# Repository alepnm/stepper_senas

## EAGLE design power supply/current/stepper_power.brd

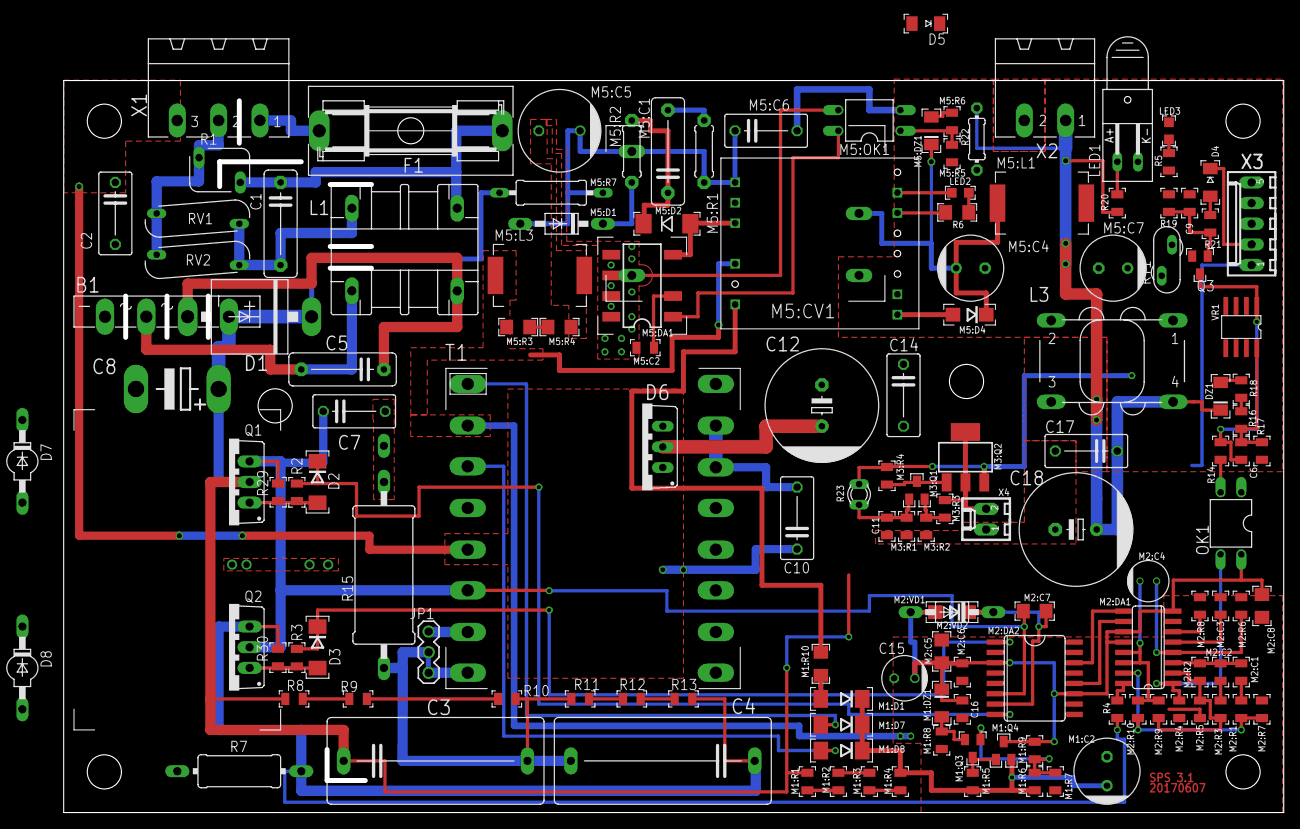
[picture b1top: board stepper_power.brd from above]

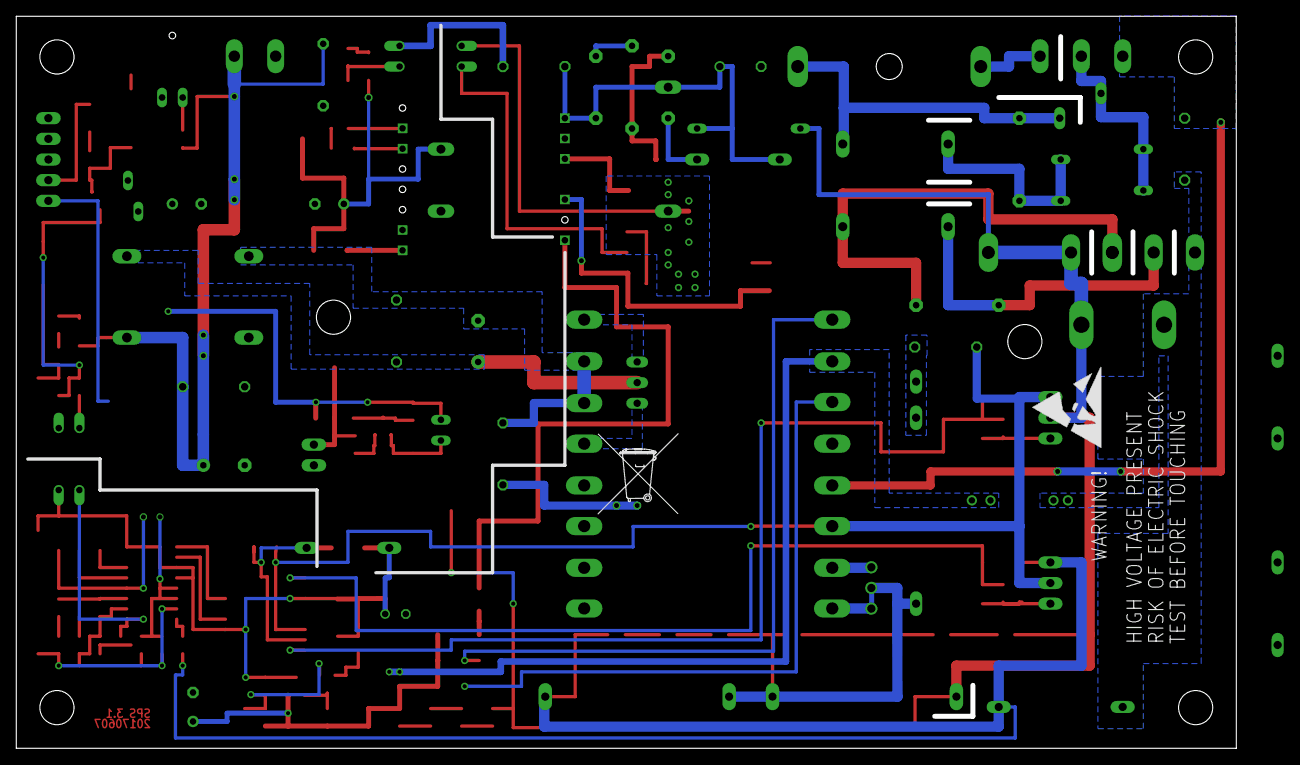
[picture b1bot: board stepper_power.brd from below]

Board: 2 copper layers, 150.0 x 90.0 mm, 143 parts (2 on the bottom side), 88 nets.

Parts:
B1: GBU8K; GBU4S
C1, C5: 0.1/400V; C102-043X133
C2, C10: 2200/3kV; C075-042X103
C3, C4: 1,0uFx275V; C225-108X268
C6, C16: 0.1; C0805
C7: 1n; C075-042X103
C8: 330,0x450V; EB25H
C9, C11: 10n; C0805
C12, C18: 1000x50V; E5-13
C14, C17: 0.1; C075-042X103
C15: 47x16V; E2,5-6E
D1: P600K; P6-15-1
D2, D3: 10MQ100; DO214AA
D4, D5: BAS32; MINIMELF
D6: MUR1620CTG; TO220ABS
D7, D8: BYV27; SOD57-10
DZ1: 12V; SOD80C
F1: 5A; SH22,5A
JP1: 1X03
L1: MFE
L3: 82721K
LED1: VOUT; Q62902-B155
LED2, LED3: 12V; CHIPLED_0805
M1:C2, M5:C4, M5:C7: 100x35V; E3,5-8
M1:D1, M1:D7, M1:D8: 10MQ100; DO214AA
M1:DZ1, M5:DZ1: 12V; SOD80C
M1:Q3: BC817; SOT23-BEC
M1:Q4: BC807; SOT23-BEC
M1:R1, M1:R2, M1:R3, M1:R4, M1:R5, M1:R6, M1:R7, M1:R8, M1:R9, M3:R1, M3:R2, M3:R3, M3:R4, M5:R5, M5:R6: R0805
M1:R10: 120; R1206
M2:C1, M2:C2: 10n; C0805
M2:C3: 4700; C0805
M2:C4: 10x63V; E2-5
M2:C5, M2:C7, M2:C8: 1uF; C1206
M2:C6, M5:C2: 0.1; C0805
M2:DA1: TL494CD; SO16
M2:DA2: IR2113S; SO16L
M2:R1, M2:R3: 33k; R0805
M2:R2: 1M; R0805
M2:R4, M2:R5, M2:R9, M2:R10: 20k; R0805
M2:R6: 10k; R0805
M2:R7: 1k; R0805
M2:R8: 2k; R0805
M2:VD1: UF4007; DO41-10
M2:VD2, M5:D4: 10MQ100; DO214AC
M3:Q1: BC817; SOT23
M3:Q2: BCP52; SOT223
M5:C1: 0.01x630V; C102-043X133
M5:C5: 10.0x400V; E5-10,5
M5:C6: 2200x3kV; C075-042X103
M5:CV1: VSK-S1-5V; VSK-S1
M5:D1: P6KE150; DO41-10
M5:D2: LL4007; MELF-MLL41
M5:DA1: TNY278G; DIP8_1
M5:L1, M5:L3: 1000uH; PLOKSCIAS
M5:OK1: PC817; DIL04
M5:R1: 100; 0207/7
M5:R2: 1k; 0207/7
M5:R3, M5:R4: 1k; R1206
M5:R7: 47; 0309/12
M5:T2: 750841630
OK1: PC817; DIL04
P1: LP_D1.0
Q1, Q2: IRF740; TO220BV
Q3: BC817; SOT23-BEC
R1: S05K275
R2, R3: 30R; R0805
R4, R29, R30: 1k; R0805
R5, R8, R9, R10, R11, R12, R13, R14, R16, R17, R18, R19, R20, R21: R0805
R6: 2k; R1206
R7: 0.1; 0411/15
R15: 100; P0817/22
R22: 10k; 0204/7
R23: P640
RT1: X40
RV1, RV2: 33; TABLETE_10
T1: ETD-39-K-H-16P
U$2: TONNE_10.00
U$3: ESD_10.00
VR1: TL431; SO-08
X1: MAIN; MSTBA3
X2: MSTBA2
X3: Stepper Control; 6410-05
X4: COOLER; 6410-02

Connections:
12VDC: M3:Q2.3, M3:R4.2, M5:C7.+, M5:L1.2, R23.1, RT1.1
12VOUT: R5.1, RT1.2, X3.3
!PS_START: D4.C, X3.2
+V: B1.+, C3.1, C8.+, D1.C, D7.C, M1:R1.2, M5:R7.1, Q1.D, R8.1
AGND: B1.-, C2.2, C8.-, C15.-, C16.2, M1:C2.-, M1:R7.2, M1:R8.2, M2:C3.2, M2:C5.2, M2:C6.1, M2:C8.2, M2:DA1.7, M2:DA2.2, M2:DA2.13, M2:DA2.15, M2:R4.1, M2:R5.1, M2:R6.1, M2:R7.1, M2:R8.1, M5:L3.1, M5:R3.1, M5:T2.4, R7.1, T1.2
COM: C11.2, LED1.K, LED3.C, M3:R1.1, M3:R2.1, M5:C4.-, M5:C6.2, M5:C7.-, M5:CV1.COM, M5:OK1.2, M5:R5.1, M5:T2.8, X2.2, X3.4, X3.5, X4.1
FB: M2:DA1.16, R4.1
GNDP: C9.1, C17.2, C18.-, L3.3, Q3.E, R17.1, R22.2, VR1.2, VR1.3, VR1.6, VR1.7
HO: D2.C, M2:DA2.8, R2.1
LO: D3.C, M2:DA2.1, R3.1
M1:N$1: M1:D1.A, M1:R10.1
M1:N$2: M1:Q3.B, M1:R6.2, M1:R7.1, M1:R9.1
M1:N$3: M1:DZ1.A, M1:Q3.E, M1:R8.1
M1:N$4: M1:Q3.C, M1:Q4.B, M1:R5.2
M1:N$5: M1:R3.1, M1:R4.2
M1:N$6: M1:C2.+, M1:D1.C, M1:D7.C, M1:D8.C, M1:Q4.E, M1:R4.1, M1:R5.1, M1:R6.1
M1:N$8: M1:R1.1, M1:R2.2
M1:N$9: M1:R2.1, M1:R3.2
M2:N$1: M2:DA1.9, M2:DA2.14
M2:N$2: M2:DA1.10, M2:DA2.12
M2:N$3: M2:C7.1, M2:DA2.7, M2:VD1.C, M2:VD2.C
M2:N$4: M2:DA1.6, M2:R8.2
M2:N$5: M2:C3.1, M2:DA1.5
M2:N$6: M2:C1.1, M2:R1.2
M2:N$7: M2:C1.2, M2:C2.1, M2:DA1.3, M2:R2.1
M2:N$8: M2:DA1.2, M2:R2.2, M2:R3.2, M2:R5.2, M2:R9.1
M2:N$9: M2:C4.+, M2:DA1.13, M2:DA1.14, M2:R9.2, M2:R10.2
M2:N$10: M2:C2.2, M2:R3.1
M2:N$11: M2:DA1.15, M2:R1.1, M2:R7.2, M2:R10.1
M2:N$12: M2:C4.-, M2:DA1.4, M2:R6.2
M3:N$1: M3:Q1.2, M3:R2.2, M3:R3.1
M3:N$2: M3:Q1.3, M3:Q2.1, M3:R4.1
M5:AGND: M5:C2.2, M5:C5.-, M5:CV1.AC2, M5:DA1.5, M5:DA1.6, M5:DA1.7, M5:DA1.8, M5:L3.2, M5:OK1.3, M5:R4.2
M5:N$1: M5:C1.2, M5:R1.1
M5:N$2: M5:D1.C, M5:R2.2
M5:N$3: M5:C5.+, M5:C6.1, M5:CV1.AC1, M5:D1.A, M5:R1.2, M5:R7.2, M5:T2.1
M5:N$4: M5:C1.1, M5:D2.C, M5:R2.1
M5:N$5: M5:C2.1, M5:DA1.2
M5:N$6: M5:D2.A, M5:DA1.4, M5:T2.3
M5:N$7: M5:C4.+, M5:CV1.VDC, M5:D4.C, M5:DZ1.C, M5:L1.1
M5:N$8: M5:DA1.1, M5:OK1.4
M5:N$10: M5:D4.A, M5:T2.7
M5:N$13: M5:OK1.1, M5:R5.2, M5:R6.1
M5:N$15: M5:R3.2, M5:R4.1
M5:N$16: M5:DZ1.A, M5:R6.2
unnamed: OK1.2, R14.2
unnamed: R11.1, R12.1
unnamed: M5:T2.12, R6.2
unnamed: C3.2, C4.2, JP1.2, R10.2, R11.2, R15.1
unnamed: C7.2, P1.P$1, R15.2
unnamed: D3.A, Q2.G, R3.2, R30.1
unnamed: D6.3, T1.16
unnamed: D6.1, T1.13
unnamed: C6.2, R16.2, R17.2, VR1.8
unnamed: DZ1.A, R18.1
unnamed: C10.2, C12.-, C14.1, L3.2, T1.14, T1.15
unnamed: C9.2, Q3.B, R19.2, R21.2
unnamed: C12.+, C14.2, D6.2, L3.1
unnamed: LED3.A, R5.2
unnamed: D2.A, Q1.G, R2.2, R29.1
unnamed: D4.A, R21.1
unnamed: C11.1, M3:Q1.1, M3:R1.2, R23.2
unnamed: R12.2, R13.2
unnamed: JP1.1, T1.7
unnamed: M3:Q2.2, M3:Q2.4, M3:R3.2, X4.2
unnamed: JP1.3, T1.8
unnamed: D5.C, LED2.A, R6.1
unnamed: D5.A, LED2.C, M5:T2.13
unnamed: R9.1, R10.1
unnamed: R8.2, R9.2
unnamed: LED1.A, R20.1
unnamed: C1.2, L1.3, RV1.1, RV2.1
unnamed: C1.1, F1.2, L1.2, R1.2
unnamed: R1.1, RV1.2, RV2.2, X1.2
unnamed: F1.1, X1.1
unnamed: C6.1, Q3.C, R14.1, VR1.1
unnamed: B1.AC2, C5.2, L1.4
unnamed: R16.1, R18.2
unnamed: C4.1, D8.A, Q2.S, R4.2, R7.2, R13.1, R30.2
unnamed: B1.AC1, C5.1, D1.A, L1.1
OKE: M2:DA1.1, M2:R4.2, OK1.3
PE: C2.1, C10.1, T1.5, X1.3
TRA: M1:D8.A, T1.3
TRB: M1:D7.A, T1.1
VB: C7.1, D7.A, D8.C, M2:C7.2, M2:DA2.6, Q1.S, Q2.D, R29.2, T1.6
VCT: M1:R10.2, M5:T2.6
VDD: C15.+, C16.1, M1:DZ1.C, M1:Q4.C, M1:R9.2, M2:C5.1, M2:C6.2, M2:C8.1, M2:DA1.8, M2:DA1.11, M2:DA1.12, M2:DA2.3, M2:DA2.11, M2:VD1.A, M2:VD2.A, OK1.4
VOUT: C17.1, C18.+, DZ1.C, L3.4, OK1.1, R19.1, R20.2, R22.1, X2.1

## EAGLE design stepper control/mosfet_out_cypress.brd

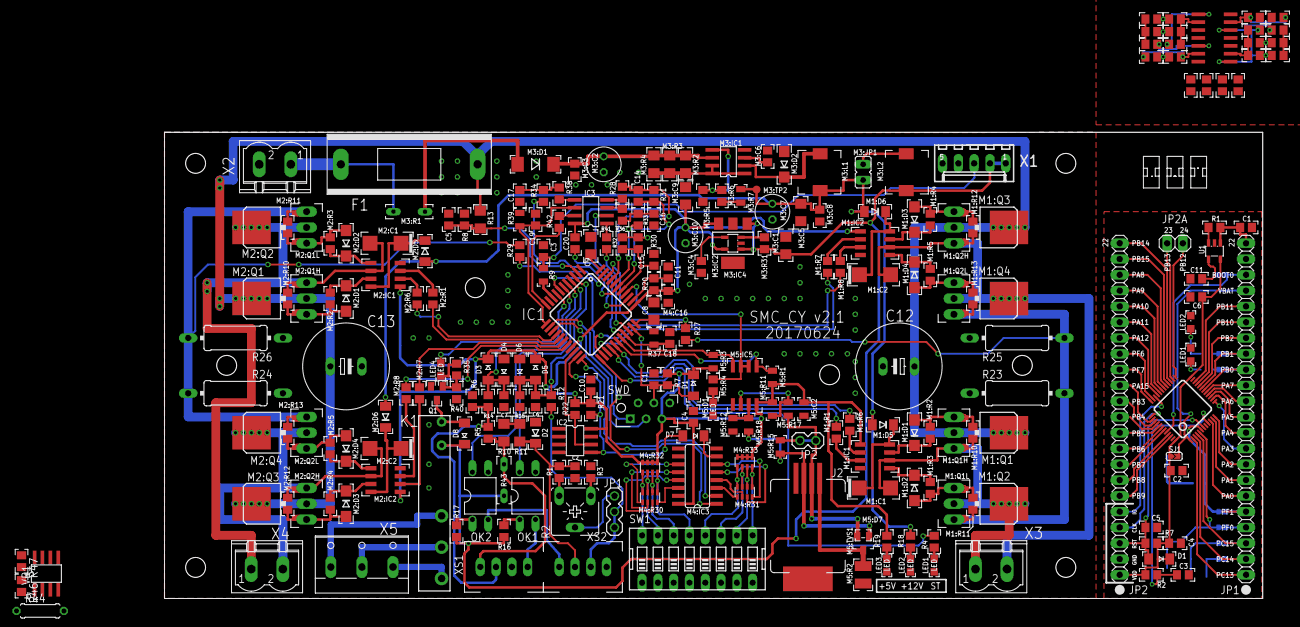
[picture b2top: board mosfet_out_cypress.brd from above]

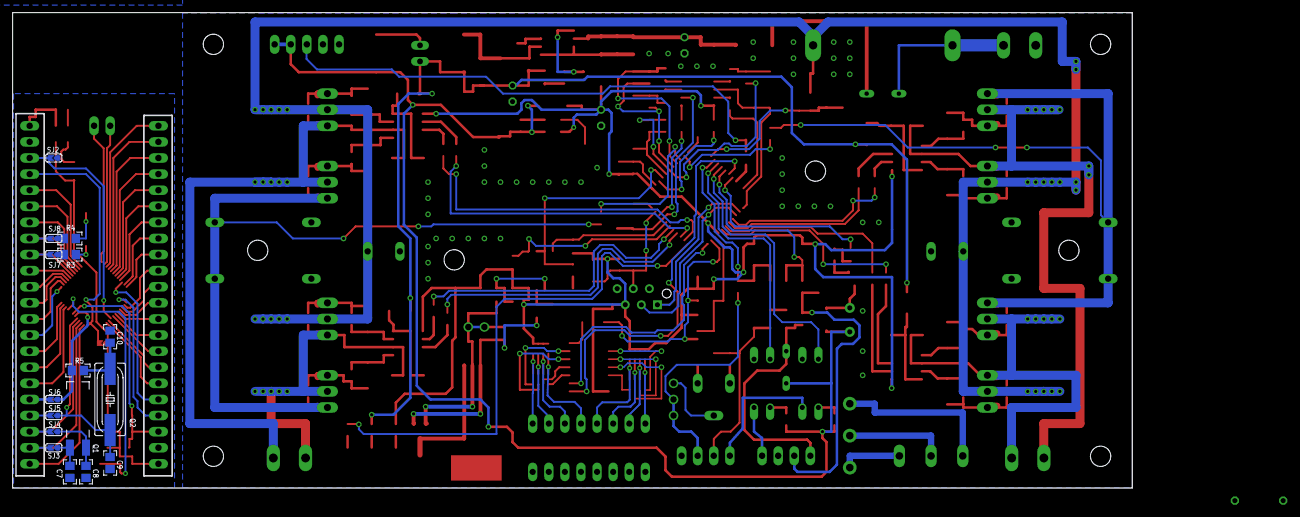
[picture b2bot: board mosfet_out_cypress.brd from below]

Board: 2 copper layers, 176.7 x 75.0 mm, 265 parts (16 on the bottom side), 214 nets.

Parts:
C1: 10nF; C0805
C2, C3, C4, C5, C6, C7, C10, C11, C20: 0.1uF; C0805
C8, C9: 1.0uF; C1206
C12, C13: 1000uF/50V; E5-13
C14, C15, C16, C17, C18, C19: 100pF; C0805
D1, D7: BAS85; MINIMELF
D2: 12V; MINIMELF
D3, D4, D5, D6, D8: BAS32; MINIMELF
F1: 8A; SH22
IC1: CY8C4245AXI; PQFP44
IC2: 24AA02SN; SO-08
IC3: LM393D; SO08
J1, J3: JUMP
J2: RS485; RJ11_SMD
JP1: 1X03
JP2: TERM; 1X02
K1: FAULT; FTR-LYC
LED1, LED2, LED3, LED4: EL19-21SYGC; CHIPLED_0805
M1:C1, M1:C2, M2:C1, M2:C2: 22uF; SMC_C
M1:D1, M1:D2, M1:D3, M1:D4, M2:D1, M2:D2, M2:D3, M2:D4, M3:D2: 10MQ100N; DO214AC
M1:D5, M1:D6, M2:D5, M2:D6: BAS32; MINIMELF
M1:IC1, M1:IC2, M2:IC1, M2:IC2: IR2101S; SO08
M1:Q1, M1:Q2, M1:Q3, M1:Q4, M2:Q1, M2:Q2, M2:Q3, M2:Q4: IRFP3607; D-PAK_TO252AA
M1:Q1H, M1:Q1L, M1:Q2H, M1:Q2L, M2:Q1H, M2:Q1L, M2:Q2H, M2:Q2L: IRF540; TO220BH_NO_HOLE
M1:R1, M1:R6, M1:R7, M1:R8, M2:R1, M2:R6, M2:R7, M2:R8: 120R; R0805
M1:R2, M1:R3, M1:R4, M1:R5, M2:R2, M2:R3, M2:R4, M2:R5: 30R; R0805
M1:R10, M1:R11, M1:R12, M1:R13, M2:R10, M2:R11, M2:R12, M2:R13, M3:R31, M5:R4: 1k; R0805
M3:C1, M3:C5, M3:C9: 1.0uF; C1206
M3:C2: 47uF/35V; E2,5-6
M3:C3, M3:C8, M4:C16: 0.1uF; C0805
M3:C4: 10nF; C0805
M3:C6: 470pF; C0805
M3:C7, M3:C10: 100uF/16V; E2,5-6
M3:D1: LL4004G; MELF-MLL41
M3:IC1: MC34063AD; SO08
M3:IC2: LM340MP-5.0; SOT223
M3:IC4: SIP21106; SOT25
M3:J1: VB power; JUMP
M3:JP1: JP1
M3:L1, M3:L2: 330uH; DR7045
M3:R1: 72V 400mA; B57164
M3:R2, M3:R3, M3:R4: 1.0R; R1206
M3:R5, M5:R1, M5:R3, M5:R11, M5:R12: 4.7k; R0805
M3:R6: 12k; R0805
M3:R7: xxx; R0805
M3:TP2: TPB1,27; B1,27
M4:IC3: 74AC165D; SO16
M4:R30, M4:R31: 120R; CTS742C083
M4:R32, M4:R33: 1k; CTS742C083
M5:C2: 0.1; C0805
M5:D1: EL19-21SYGC; CHIPLED_0805
M5:D7: PESD1LIN; SOD323-R
M5:IC5: MAX485; ESOP-8
M5:R2: 100R; R1210
M5:R15: 120; R0805
M5:R17, M5:R18: 47R; R0805
M5:TVS1: SM712; SOT23
OK1, OK2: PC817; DIL04
Q1: BC817; SOT23-BEC
R1, R3, R4, R19, R20: 120R; R0805
R2: 10k; CA6V
R5, R6, R21, R22, R35: 4.7k; R0805
R7: 15k; R0805
R8: 22k; R1206
R9, R12, R14, R15, R31, R32, R40: 10k; R0805
R10, R11: 120R; R1206
R13, R27, R28, R29, R30: 2k; R0805
R16, R17, R18, R33, R34, R36, R38: 1k; R0805
R23, R24, R25, R26: 0.1; 0411/15
R37, R39: 1.8k; R0805
R41, R42: 22R; R0805
R43: 60V 50mA; B57164
R44: 24R; 0207/7
R46: 9.1k; R0805
R47: 3k; R0805
STM:C1, STM:C2, STM:C3, STM:C4, STM:C6: 0.1uF; C0805
STM:C5, STM:C11: 10nF; C0805
STM:C7, STM:C8, STM:C9, STM:C10: 33pF; C0805
STM:C12, STM:C13, STM:C14, STM:C15, STM:C16, STM:C17: 100pF; C0805
STM:D1: BAS85; MINIMELF
STM:IC1: STM32F051C6T; TQFP48
STM:IC2: LM2902D; SO14
STM:JP1, STM:JP2: 1X22
STM:JP2A: 1X02
STM:LED1, STM:LED2: EL19-21SYGC; CHIPLED_0805
STM:Q1: 32k; TC38H
STM:Q2: SM49
STM:R1, STM:R9, STM:R20: 10k; R0805
STM:R2: 120R; R0805
STM:R3, STM:R4, STM:R10, STM:R11, STM:R12, STM:R15, STM:R16, STM:R17, STM:R18, STM:R19: 1k; R0805
STM:R5: 330R; R0805
STM:R6, STM:R8, STM:R13, STM:R14: 2k; R0805
STM:R7: 15k; R0805
STM:SJ1, STM:SJ2, STM:SJ3, STM:SJ4, STM:SJ5, STM:SJ6, STM:SJ7, STM:SJ8: SJA
STM:U1: SIP21106-DT-33-E3; SOT25
SW1: DIPSWITCH-08
SWD: SWD; ISP
VR1: TL431D; SO-08
X1: 6410-05
X2: Power; MSTBV2
X3: WIND A; MSTBV2
X4: WIND B; MSTBV2
X5: FAULT; W237-103
XS1, XS2: ZALIA_4K

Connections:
10VDC: C2.1, D2.C, R1.2, R11.1, R44.1, R46.2, VR1.1, XS2.2
!M1PWMA: IC1.26, M1:R1.1
!M1PWMB: IC1.24, M1:R8.1
!M2PWMA: IC1.16, M2:R1.1
!M2PWMB: IC1.18, M2:R8.1
!NRST: C1.1, D1.A, IC1.32, R7.2, SWD.4
!WA: M1:C2.-, M1:IC2.6, M1:Q2H.S, M1:Q2L.D, M1:Q3.3, M1:Q4.4, M1:R12.1, X3.2
!WB: M2:C2.-, M2:IC2.6, M2:Q2H.S, M2:Q2L.D, M2:Q3.3, M2:Q4.4, M2:R12.1, X4.2
DI0: OK1.2, XS1.4
DI0/STEP: IC1.4, OK1.4
DI1: OK2.2, XS2.1
DI1/DIR: IC1.5, OK2.4
DI2/ENA: C7.1, D3.A, D4.C, IC1.6, R14.2
DO0/RELAY: IC1.8, LED4.A
DO1/VBEN: IC1.9, R9.2
GND: C1.2, C2.2, C3.2, C4.2, C5.2, C6.2, C7.2, C8.1, C9.1, C10.2, C11.1, C12.-, C13.-, C16.2, C17.2, C18.2, C19.2, D2.A, D4.A, D6.A, IC1.1, IC1.10, IC2.1, IC2.2, IC2.3, IC2.4, IC2.7, IC3.4, LED1.C, LED2.C, LED3.C, M1:IC1.4, M1:IC2.4, M2:IC1.4, M2:IC2.4, M3:C1.2, M3:C2.-, M3:C3.2, M3:C4.2, M3:C5.2, M3:C6.2, M3:C7.-, M3:C8.2, M3:C9.2, M3:C10.-, M3:D2.A, M3:IC1.4, M3:IC2.2, M3:IC2.4, M3:IC4.2, M3:R5.1, M4:C16.2, M4:IC3.8, M4:IC3.15, M5:C2.2, M5:D1.C, M5:IC5.5, M5:R2.1, M5:R12.1, OK1.3, OK2.3, Q1.E, R3.1, R6.2, R13.1, R15.2, R23.1, R24.1, R25.1, R26.1, R28.1, R30.1, R37.2, R39.2, R40.2, R47.1, STM:C1.2, STM:C2.2, STM:C3.2, STM:C4.2, STM:C5.2, STM:C6.2, STM:C7.2, STM:C8.2, STM:C9.2, STM:C10.2, STM:C11.2, STM:C13.2, STM:C14.2, STM:C15.2, STM:C16.2, STM:IC1.8, STM:IC1.23, STM:IC1.47, STM:IC2.11, STM:JP1.21, STM:JP2.2, STM:LED1.C, STM:LED2.C, STM:R8.2, STM:R12.2, STM:R14.2, STM:R17.2, STM:SJ2.1, STM:U1.2, SW1.1, SW1.2, SW1.3, SW1.4, SW1.5, SW1.6, SW1.7, SW1.8, SWD.2, SWD.6, VR1.2, VR1.3, VR1.6, VR1.7, X1.4, X1.5, X2.2, XS1.3, XS2.4
GNDA: C20.2, IC1.36
IA: M1:Q1L.S, M1:Q2.3, M1:Q2L.S, M1:Q4.3, M1:R11.1, M1:R13.2, R23.2, R25.2, R27.1
IAN: C14.2, IC1.41, R28.2, R31.1
IAO: C14.1, IC1.40, R31.2, R33.2
IAP: IC1.42, R27.2
IAREF: C18.1, IC1.30, IC3.2, R37.1
IB: M2:Q1L.S, M2:Q2.3, M2:Q2L.S, M2:Q4.3, M2:R11.1, M2:R13.2, R24.2, R26.2, R29.1
IBN: C15.2, IC1.38, R30.2, R32.1
IBO: C15.1, IC1.39, R32.2, R34.2
IBP: IC1.43, R29.2
IBREF: C19.1, IC1.12, IC3.6, R39.1
M1:AH: M1:D1.C, M1:IC1.7, M1:R2.1
M1:AL: M1:D2.C, M1:IC1.5, M1:R3.1
M1:BH: M1:D3.C, M1:IC2.7, M1:R4.2
M1:BL: M1:D4.C, M1:IC2.5, M1:R5.2
M1:N$1: M1:C2.+, M1:D6.C, M1:IC2.8
M1:N$2: M1:C1.+, M1:D5.C, M1:IC1.8
M1:N$3: M1:IC1.3, M1:R1.2
M1:N$4: M1:IC1.2, M1:R6.2
M1:N$5: M1:D1.A, M1:Q1.1, M1:Q1H.G, M1:R2.2, M1:R10.1
M1:N$6: M1:IC2.2, M1:R7.2
M1:N$7: M1:D2.A, M1:Q1L.G, M1:Q2.1, M1:R3.2, M1:R11.2
M1:N$8: M1:IC2.3, M1:R8.2
M1:N$9: M1:D3.A, M1:Q2H.G, M1:Q3.1, M1:R4.1, M1:R12.2
M1:N$11: M1:D4.A, M1:Q2L.G, M1:Q4.1, M1:R5.1, M1:R13.1
M1PWMA: IC1.27, M1:R6.1
M1PWMB: IC1.25, M1:R7.1
M2:AH: M2:D1.C, M2:IC1.7, M2:R2.1
M2:AL: M2:D2.C, M2:IC1.5, M2:R3.1
M2:BH: M2:D3.C, M2:IC2.7, M2:R4.2
M2:BL: M2:D4.C, M2:IC2.5, M2:R5.2
M2:N$1: M2:C2.+, M2:D6.C, M2:IC2.8
M2:N$2: M2:C1.+, M2:D5.C, M2:IC1.8
M2:N$3: M2:IC1.3, M2:R1.2
M2:N$4: M2:IC1.2, M2:R6.2
M2:N$5: M2:D1.A, M2:Q1.1, M2:Q1H.G, M2:R2.2, M2:R10.1
M2:N$6: M2:IC2.2, M2:R7.2
M2:N$7: M2:D2.A, M2:Q1L.G, M2:Q2.1, M2:R3.2, M2:R11.2
M2:N$8: M2:IC2.3, M2:R8.2
M2:N$9: M2:D3.A, M2:Q2H.G, M2:Q3.1, M2:R4.1, M2:R12.2
M2:N$11: M2:D4.A, M2:Q2L.G, M2:Q4.1, M2:R5.1, M2:R13.1
M2PWMA: IC1.15, M2:R6.1
M2PWMB: IC1.17, M2:R7.1
M3:N$1: M3:JP1.1, M3:L2.1
M3:N$2: M3:C4.1, M3:IC4.4
M3:N$3: M3:IC1.1, M3:IC1.7, M3:IC1.8, M3:R2.2, M3:R3.2, M3:R4.2
M3:N$4: M3:IC1.5, M3:R5.2, M3:R6.1
M3:N$5: M3:C6.1, M3:IC1.3
M3:N$6: M3:R6.2, M3:R7.1
M3:N$7: M3:C2.+, M3:C3.1, M3:D1.C, M3:IC1.6, M3:R2.1, M3:R3.1, M3:R4.1
M3:N$8: M3:D2.C, M3:IC1.2, M3:L1.2
M3:N$9: M3:IC4.3, M3:R31.2
M3:N$16: M3:D1.A, M3:R1.2
M4:N$1: M4:IC3.6, M4:R31.4A
M4:N$2: M4:IC3.5, M4:R31.3A
M4:N$3: M4:IC3.4, M4:R31.2A
M4:N$4: M4:IC3.3, M4:R31.1A
M4:N$5: M4:IC3.11, M4:R30.1A
M4:N$6: M4:IC3.12, M4:R30.2A
M4:N$7: M4:IC3.13, M4:R30.3A
M4:N$8: M4:IC3.14, M4:R30.4A
M5:N$2: M5:IC5.7, M5:R12.2, M5:R18.1
M5:N$3: M5:IC5.6, M5:R11.2, M5:R17.1
M5:N$4: M5:D1.A, M5:R4.2
unnamed: IC3.7, R42.1
unnamed: D7.C, M4:IC3.7
unnamed: IC3.1, R41.1
unnamed: C11.2, IC1.35, R20.2
unnamed: IC3.3, R36.1
unnamed: IC3.5, R38.1
unnamed: JP1.1, R2.S
unnamed: R2.A, R3.2
unnamed: JP1.2, R12.2
unnamed: JP1.3, XS2.3
unnamed: R10.1, R11.2
unnamed: JP2.2, M5:R15.2
unnamed: M4:R31.4B, M4:R33.4A, SW1.9
unnamed: R1.1, R2.E
unnamed: M4:R31.3B, M4:R33.3A, SW1.10
unnamed: M4:R31.2B, M4:R33.2A, SW1.11
unnamed: C16.1, R33.1, R36.2
unnamed: C17.1, R34.1, R38.2
unnamed: M4:R31.1B, M4:R33.1A, SW1.12
unnamed: M4:R30.4B, M4:R32.4A, SW1.13
unnamed: M4:R30.3B, M4:R32.3A, SW1.14
unnamed: M4:R30.2B, M4:R32.2A, SW1.15
unnamed: M4:R30.1B, M4:R32.1A, SW1.16
unnamed: Q1.B, R35.2, R40.1
unnamed: D8.A, K1.1, Q1.C
unnamed: K1.4, X5.2
unnamed: K1.5, X5.3
unnamed: K1.3, X5.1
unnamed: J2.2, M5:D7.A, M5:R15.1, M5:R18.2, M5:TVS1.1
unnamed: J2.3, JP2.1, M5:D7.C, M5:R17.2, M5:TVS1.2
unnamed: J2.4, M5:R2.2, M5:TVS1.3
unnamed: R5.2, R6.1, R14.1, XS1.2
unnamed: LED1.A, R4.1
unnamed: LED2.A, R18.1
unnamed: LED3.A, R19.1
unnamed: LED4.C, R35.1
unnamed: OK1.1, R16.1
unnamed: R5.1, R10.2, R43.2, XS1.1
unnamed: OK2.1, R17.1
unnamed: R46.1, R47.2, VR1.8
unnamed: C9.2, IC1.44
unnamed: C8.2, IC1.33
SPEED: C6.1, D5.A, D6.C, IC1.3, R12.1, R15.1
SPI_LAT: IC1.7, M4:IC3.1
SPI_MISO: D7.A, IC1.21, IC2.5, R21.2
SPI_MOSI: IC1.20, IC2.6, R22.1
SPI_SCK: IC1.22, M4:IC3.2
STATUS_LED: IC1.23, R4.2
STM:!NRST: STM:C5.1, STM:D1.A, STM:IC1.7, STM:JP2.3, STM:R7.2
STM:BOOT0: STM:IC1.44, STM:JP1.20, STM:SJ2.2
STM:IAREF: STM:C14.1, STM:IC2.6, STM:R12.1
STM:IBREF: STM:C16.1, STM:IC2.13, STM:R17.1
STM:N$1: STM:C7.1, STM:Q1.1, STM:SJ3.1
STM:N$2: STM:C8.1, STM:Q1.2, STM:SJ4.1
STM:N$3: STM:C10.1, STM:Q2.2, STM:R5.2
STM:N$4: STM:IC2.3, STM:R6.1
STM:N$5: STM:LED1.A, STM:R3.2
STM:N$6: STM:R3.1, STM:SJ7.1
STM:N$7: STM:C11.1, STM:U1.4
STM:N$8: STM:R1.2, STM:U1.3
STM:N$9: STM:LED2.A, STM:R4.2
STM:N$10: STM:R4.1, STM:SJ8.1
STM:N$11: STM:C12.1, STM:IC2.2, STM:R8.1, STM:R9.2
STM:N$13: STM:C12.2, STM:IC2.1, STM:R9.1, STM:R10.2
STM:N$14: STM:C13.1, STM:R10.1, STM:R11.2
STM:N$15: STM:IC2.5, STM:R11.1
STM:N$17: STM:IC2.10, STM:R13.1
STM:N$18: STM:C17.2, STM:IC2.8, STM:R15.2, STM:R20.1
STM:N$19: STM:C15.1, STM:R15.1, STM:R16.2
STM:N$20: STM:IC2.12, STM:R16.1
STM:N$21: STM:C17.1, STM:IC2.9, STM:R14.1, STM:R20.2
STM:N$23: STM:IC2.7, STM:R19.2
STM:N$24: STM:IC2.14, STM:R18.2
STM:OSCIN: STM:C9.1, STM:IC1.5, STM:Q2.1, STM:SJ5.1
STM:OSCOUT: STM:IC1.6, STM:R5.1, STM:SJ6.1
STM:PA0: STM:IC1.10, STM:JP1.6
STM:PA1: STM:IC1.11, STM:JP1.7
STM:PA2: STM:IC1.12, STM:JP1.8
STM:PA3: STM:IC1.13, STM:JP1.9
STM:PA4: STM:IC1.14, STM:JP1.10
STM:PA5: STM:IC1.15, STM:JP1.11
STM:PA6: STM:IC1.16, STM:JP1.12
STM:PA7: STM:IC1.17, STM:JP1.13
STM:PA8: STM:IC1.29, STM:JP2.20
STM:PA9: STM:IC1.30, STM:JP2.19
STM:PA10: STM:IC1.31, STM:JP2.18
STM:PA11: STM:IC1.32, STM:JP2.17
STM:PA12: STM:IC1.33, STM:JP2.16
STM:PA15: STM:IC1.38, STM:JP2.13
STM:PB0: STM:IC1.18, STM:JP1.14, STM:SJ7.2
STM:PB1: STM:IC1.19, STM:JP1.15, STM:SJ8.2
STM:PB2: STM:IC1.20, STM:JP1.16
STM:PB3: STM:IC1.39, STM:JP2.12
STM:PB4: STM:IC1.40, STM:JP2.11
STM:PB5: STM:IC1.41, STM:JP2.10
STM:PB6: STM:IC1.42, STM:JP2.9
STM:PB7: STM:IC1.43, STM:JP2.8
STM:PB8: STM:IC1.45, STM:JP2.7
STM:PB9: STM:IC1.46, STM:JP2.6
STM:PB10: STM:IC1.21, STM:JP1.17
STM:PB11: STM:IC1.22, STM:JP1.18
STM:PB12: STM:IC1.25, STM:JP2A.2
STM:PB13: STM:IC1.26, STM:JP2A.1
STM:PB14: STM:IC1.27, STM:JP2.22
STM:PB15: STM:IC1.28, STM:JP2.21
STM:PC13: STM:IC1.2, STM:JP1.1
STM:PC14: STM:IC1.3, STM:JP1.2, STM:SJ3.2
STM:PC15: STM:IC1.4, STM:JP1.3, STM:SJ4.2
STM:PF0: STM:JP1.4, STM:SJ5.2
STM:PF1: STM:JP1.5, STM:SJ6.2
STM:PF6: STM:IC1.35, STM:JP2.15
STM:PF7: STM:IC1.36, STM:JP2.14
STM:SWCLK: STM:IC1.37, STM:JP2.4
STM:SWDIO: STM:IC1.34, STM:JP2.5
STM:VBAT: STM:IC1.1, STM:JP1.19, STM:SJ1.2
STM:VDD: STM:C2.1, STM:C4.1, STM:C6.1, STM:D1.C, STM:IC1.24, STM:IC1.48, STM:JP2.1, STM:R2.1, STM:R7.1, STM:SJ1.1, STM:U1.5
STM:VDDA: STM:C3.1, STM:IC1.9, STM:R2.2
STM:VDDIN: STM:C1.1, STM:JP1.22, STM:R1.1, STM:U1.1
SWCLK: IC1.14, SWD.3
SWDIO: IC1.13, SWD.1
TASTOP: IC1.31, R41.2
TBSTOP: IC1.11, R42.2
UART_DE: IC1.37, M5:IC5.2, M5:IC5.3, M5:R4.1
UART_RX: IC1.28, M5:IC5.1, M5:R1.2
UART_TX: IC1.29, M5:IC5.4, M5:R3.2
VBENOUT: C3.1, R9.1, X1.3
VBFUSED: C12.+, C13.+, F1.2, M1:Q1.4, M1:Q1H.D, M1:Q2H.D, M1:Q3.4, M2:Q1.4, M2:Q1H.D, M2:Q2H.D, M2:Q3.4, R8.2
VBIN: F1.1, M3:R1.1, X2.1
VBUS: C5.1, IC1.2, R8.1, R13.2
VCC: M1:D5.A, M1:D6.A, M2:D5.A, M2:D6.A, M3:C5.1, M3:C7.+, M3:C8.1, M3:JP1.2, M3:L1.1, M3:R7.2, M3:TP2.PP, R18.2
VDD: C4.1, C10.1, C20.1, D1.C, D3.C, D5.C, IC1.19, IC1.34, IC2.8, IC3.8, M1:IC1.1, M1:IC2.1, M2:IC1.1, M2:IC2.1, M3:C9.1, M3:C10.+, M3:IC2.3, M3:IC4.5, M4:C16.1, M4:IC3.16, M4:R32.1B, M4:R32.2B, M4:R32.3B, M4:R32.4B, M4:R33.1B, M4:R33.2B, M4:R33.3B, M4:R33.4B, M5:C2.1, M5:IC5.8, M5:R1.1, M5:R3.1, M5:R11.1, R7.1, R19.2, R20.1, R21.1, R22.2, SWD.5
VDDIN: D8.C, K1.2, M3:C1.1, M3:IC2.1, M3:IC4.1, M3:L2.2, M3:R31.1, R16.2, R17.2, R43.1, R44.2, X1.1, X1.2
WA: M1:C1.-, M1:IC1.6, M1:Q1.3, M1:Q1H.S, M1:Q1L.D, M1:Q2.4, M1:R10.2, X3.1
WB: M2:C1.-, M2:IC1.6, M2:Q1.3, M2:Q1H.S, M2:Q1L.D, M2:Q2.4, M2:R10.2, X4.1

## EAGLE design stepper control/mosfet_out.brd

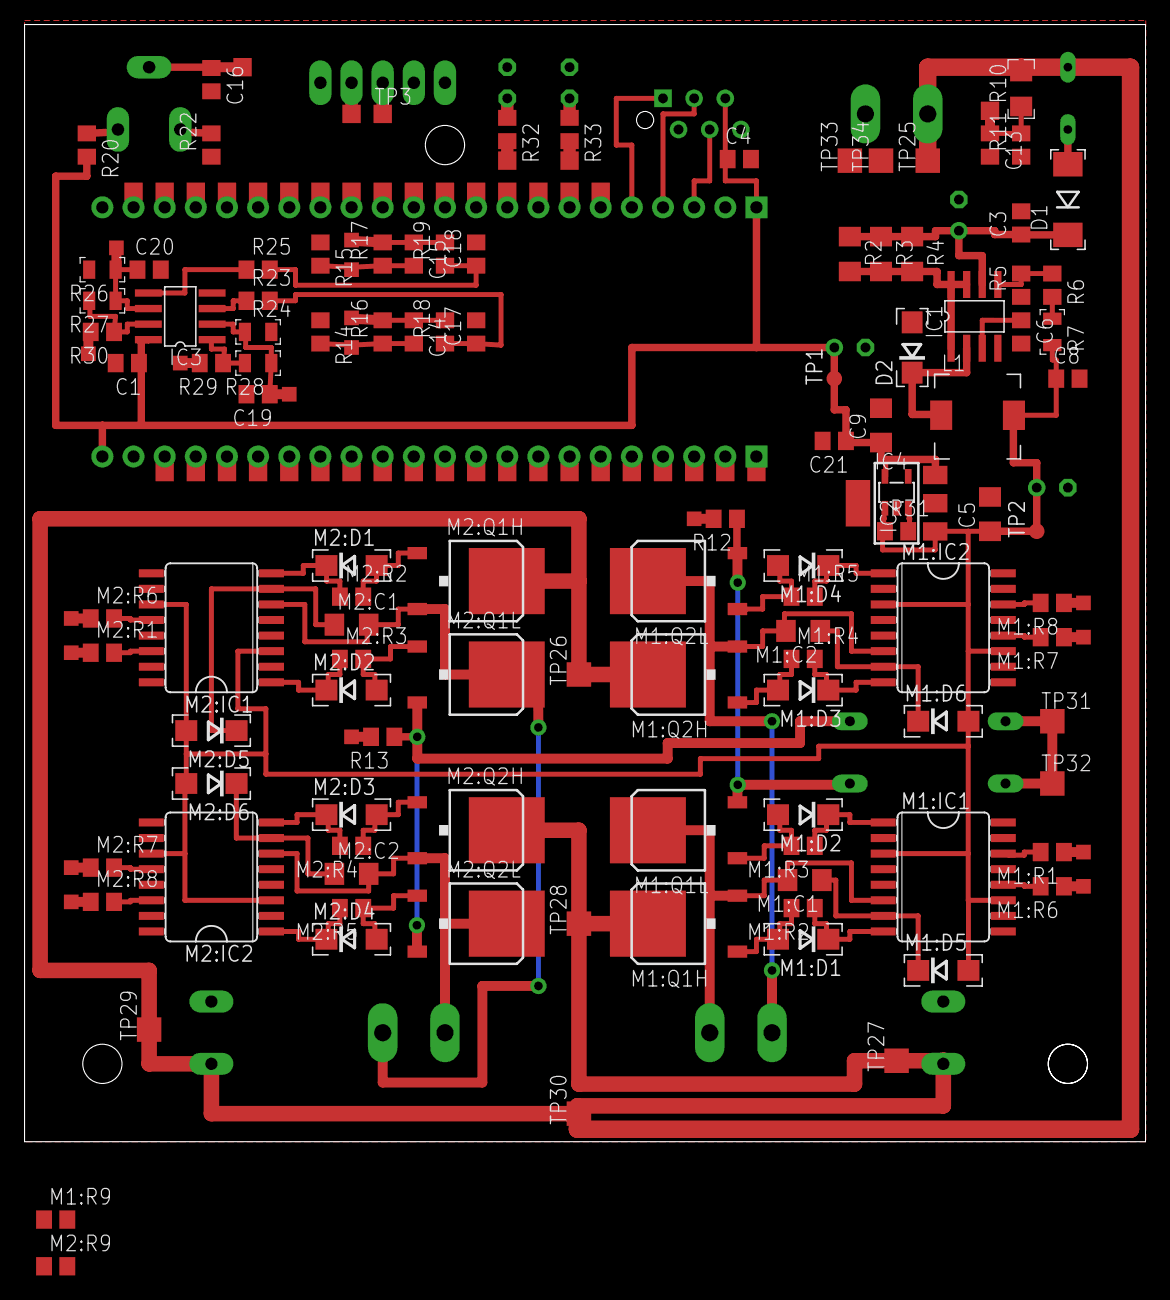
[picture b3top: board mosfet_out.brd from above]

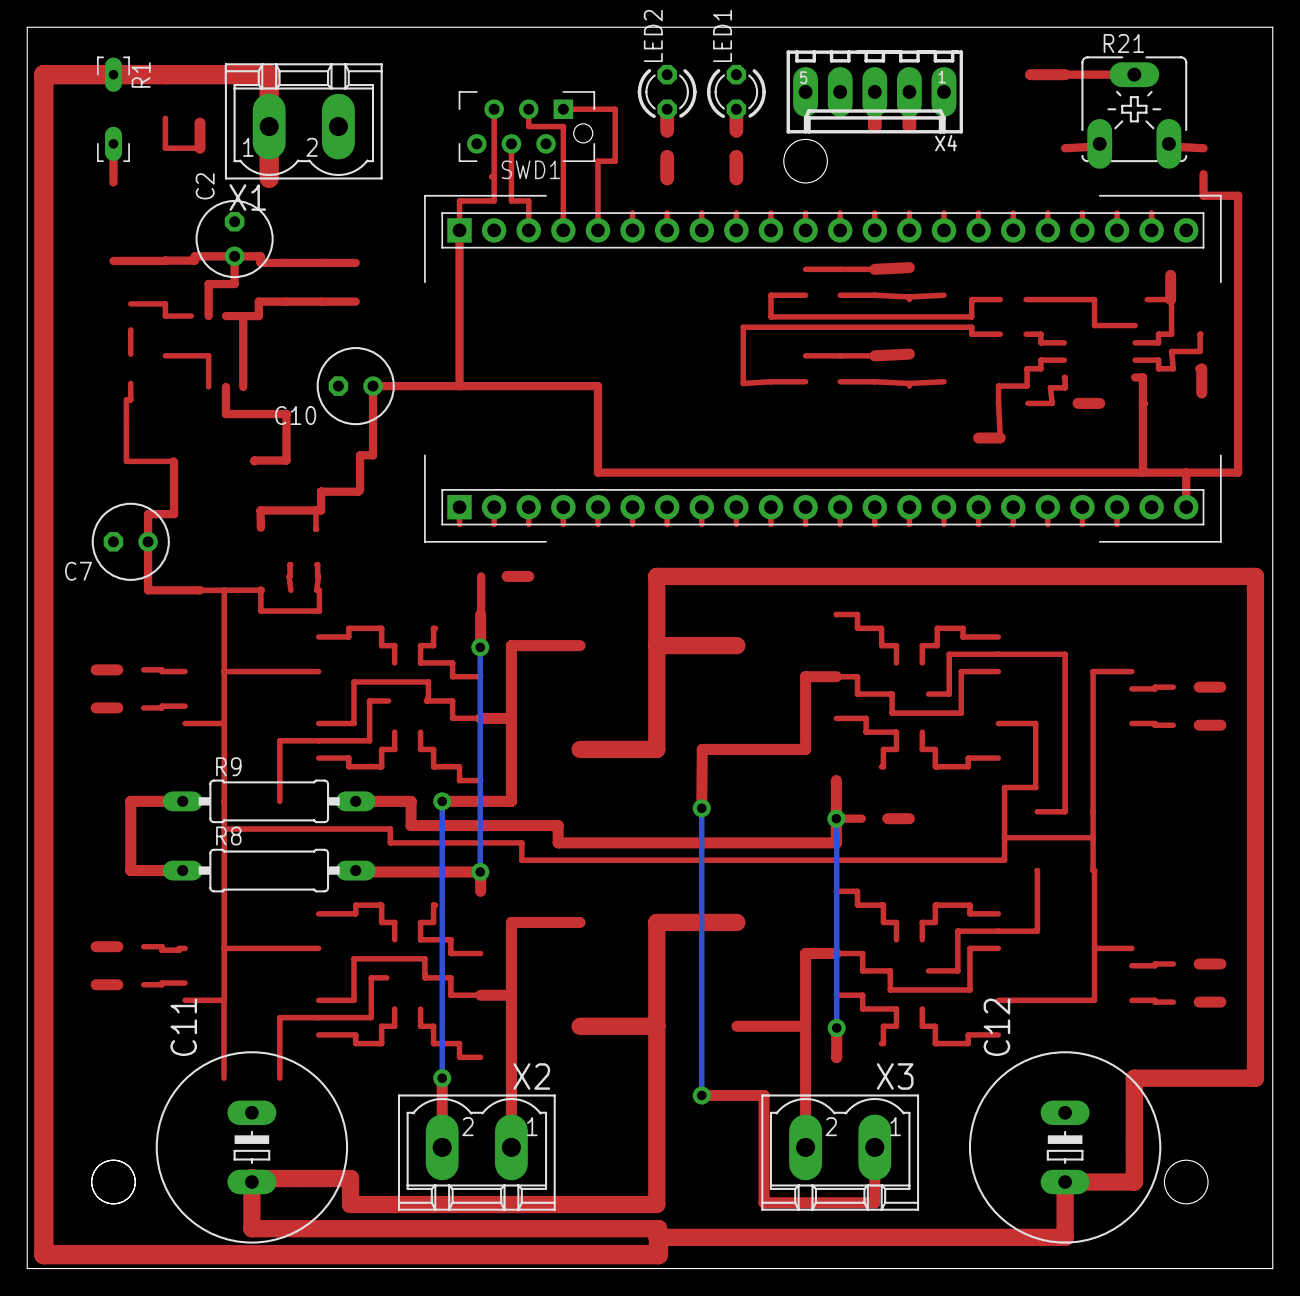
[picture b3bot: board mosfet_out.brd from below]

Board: 2 copper layers, 91.4 x 91.1 mm, 187 parts (17 on the bottom side), 115 nets.

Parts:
C1, C3, C4, C8, C13, C16, C21: 0.1uF; C0805
C2: 47uF/35V; E2,5-6
C5, C9: 1.0uF; C1206
C6: 470pF; C0805
C7, C10: 100uF/16V; E2,5-6
C11, C12: 1000uF/50V; E5-13
C14, C15, C17, C18, C19, C20: 100pF; C0805
D1: LL4004G; MELF-MLL41
D2: 10MQ100N; DO214AC
IC1: MC34063AD; SO08
IC2: LM340MP-5.0; SOT223
IC3: LM393D; SO08
IC4: SIP21106-DT-33-E3; SOT25
L1: 330uH; DR7045
LED1, LED2: LED3MM
M1:C1, M1:C2, M2:C1, M2:C2: 1.0uF; C1206
M1:D1, M1:D2, M1:D3, M1:D4, M1:D5, M1:D6, M2:D1, M2:D2, M2:D3, M2:D4, M2:D5, M2:D6: 10MQ100N; DO214AC
M1:IC1, M1:IC2, M2:IC1, M2:IC2: IR2113S; SO16L
M1:Q1H, M1:Q1L, M1:Q2H, M1:Q2L, M2:Q1H, M2:Q1L, M2:Q2H, M2:Q2L: IRF3607; D-PAK_TO252AA
M1:R1, M1:R6, M1:R7, M1:R8, M1:R9, M2:R1, M2:R6, M2:R7, M2:R8, M2:R9: 100R; R0805
M1:R2, M1:R3, M1:R4, M1:R5, M2:R2, M2:R3, M2:R4, M2:R5: 22R; R0805
P0.0, P0.1, P0.2, P0.3, P1.0, P1.1, P1.2, P1.3, P1.4, P1.5, P2.2, P2.3, P3.0, P3.1, P3.4, P3.5, P3.6, P3.7: CONT_1.2MM; TP1.2X1.2
P1, P2, P2.0, P2.1, P3, P4, P5, P6, P7, P8, P9, P10, P11, P12, P13, P14, P15, P16, P17, P18, P19, P20, P21, P22, P23, P24, P25, P26, P27, P28, P29, P30, P31, P32, P33, P34, P35, P36, P57, P58, P60: CONT_1.5MM; TP1.5X1.5
R1: 72V 400mA; B57164
R2, R3, R4: 1.0R; R1206
R5: 4.7k; R0805
R6: 12k; R0805
R7, R27, R28: R0805
R8, R9: 0.03; 0309/12
R10: 19.1k; R1206
R11, R12, R13, R14, R15, R32, R33: 2k; R0805
R16, R17: 10k; R0805
R18, R19, R23, R25, R31: 1k; R0805
R20, R22: 330R; R0805
R21: 10k; CA6V
R24, R26: 1.8k; R0805
R29, R30: 22R; R0805
SWD1: SWD; ISP
TP1, TP2: TPB1,27; B1,27
TP3: TPTP15SQ; TP15SQ
TP25, TP26, TP27, TP28, TP29, TP30, TP31, TP32, TP33, TP34: TPTP20SQ; TP20SQ
U1: CY8CKIT-049-42XX
X1: POWER; MSTBV2
X2: WIND A; MSTBV2
X3: WIND B; MSTBV2
X4: 6410-05

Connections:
12VDC: C5.1, C7.+, C8.1, IC2.1, IC4.1, L1.1, M1:D5.A, M1:D6.A, M1:IC1.3, M1:IC1.11, M1:IC2.3, M1:IC2.11, M2:D5.A, M2:D6.A, M2:IC1.3, M2:IC1.11, M2:IC2.3, M2:IC2.11, R7.2, R31.1, TP2.PP, TP3.TP, X4.3
!WA: M1:C2.2, M1:IC2.6, M1:Q2H.3, M1:Q2L.4, X2.2
!WB: M2:C2.2, M2:IC2.6, M2:Q2H.3, M2:Q2L.4, X3.2
GND: C1.2, C2.-, C3.2, C4.2, C5.2, C6.2, C7.-, C8.2, C9.2, C10.-, C11.-, C12.-, C13.2, C16.2, C17.2, C18.2, C19.2, C20.2, C21.2, D2.A, IC1.4, IC2.2, IC2.4, IC3.4, IC4.2, LED1.C, LED2.C, M1:IC1.2, M1:IC1.13, M1:IC1.15, M1:IC2.2, M1:IC2.13, M1:IC2.15, M1:R9.2, M2:IC1.2, M2:IC1.13, M2:IC1.15, M2:IC2.2, M2:IC2.13, M2:IC2.15, M2:R9.2, R5.1, R11.1, R14.1, R15.1, R22.1, R24.2, R26.2, SWD1.2, SWD1.6, TP33.TP, TP34.TP, U1.2, U1.22, U1.43, X1.2, X4.4, X4.5
GNDA: R8.1, R9.1, TP31.TP, TP32.TP
IA: M1:Q1L.3, M1:Q2L.3, R8.2, R12.1
IAN: C14.2, P1.4.P, P18.P, R14.2, R16.1, U1.39
IAO: C14.1, P1.3.P, P29.P, R16.2, R18.2, U1.38
IAP: P28.P, U1.40
IAREF: C19.1, IC3.2, P3.0.P, R24.1, R28.1
IA_KILL: M1:R9.1, P2.2.P, R29.2
IB: M2:Q1L.3, M2:Q2L.3, R9.2, R13.1
IBN: C15.2, P1.1.P, P30.P, R15.2, R17.1, U1.36
IBO: C15.1, P1.2.P, P19.P, R17.2, R19.2, U1.37
IBREF: C20.1, IC3.6, P3.1.P, R26.1, R27.1
IB_KILL: M2:R9.1, P2.3.P, R30.2
ICP: P20.P, U1.35
M1:AH: M1:D1.C, M1:IC1.8, M1:R2.1
M1:AL: M1:D2.C, M1:IC1.1, M1:R3.1
M1:BH: M1:D3.C, M1:IC2.8, M1:R4.2
M1:BL: M1:D4.C, M1:IC2.1, M1:R5.2
M1:N$1: M1:C2.1, M1:D6.C, M1:IC2.7
M1:N$2: M1:C1.1, M1:D5.C, M1:IC1.7
M1:N$3: M1:IC1.14, M1:R1.2
M1:N$4: M1:IC1.12, M1:R6.2
M1:N$5: M1:D1.A, M1:Q1H.1, M1:R2.2
M1:N$6: M1:IC2.12, M1:R7.2
M1:N$7: M1:D2.A, M1:Q1L.1, M1:R3.2
M1:N$8: M1:IC2.14, M1:R8.2
M1:N$9: M1:D3.A, M1:Q2H.1, M1:R4.1
M1:N$11: M1:D4.A, M1:Q2L.1, M1:R5.1
M2:AH: M2:D1.C, M2:IC1.8, M2:R2.1
M2:AL: M2:D2.C, M2:IC1.1, M2:R3.1
M2:BH: M2:D3.C, M2:IC2.8, M2:R4.2
M2:BL: M2:D4.C, M2:IC2.1, M2:R5.2
M2:N$1: M2:C2.1, M2:D6.C, M2:IC2.7
M2:N$2: M2:C1.1, M2:D5.C, M2:IC1.7
M2:N$3: M2:IC1.14, M2:R1.2
M2:N$4: M2:IC1.12, M2:R6.2
M2:N$5: M2:D1.A, M2:Q1H.1, M2:R2.2
M2:N$6: M2:IC2.12, M2:R7.2
M2:N$7: M2:D2.A, M2:Q1L.1, M2:R3.2
M2:N$8: M2:IC2.14, M2:R8.2
M2:N$9: M2:D3.A, M2:Q2H.1, M2:R4.1
M2:N$11: M2:D4.A, M2:Q2L.1, M2:R5.1
unnamed: IC3.7, R27.2, R30.1
unnamed: SWD1.1, U1.5
unnamed: IC3.1, R28.2, R29.1
unnamed: SWD1.3, U1.4
unnamed: IC3.3, R23.1
unnamed: IC3.5, R25.1
unnamed: SWD1.4, U1.3
unnamed: R21.A, R22.2
unnamed: IC1.1, IC1.7, IC1.8, R2.2, R3.2, R4.2
unnamed: IC1.5, R5.2, R6.1
unnamed: C6.1, IC1.3
unnamed: R6.2, R7.1
unnamed: C2.+, C3.1, D1.C, IC1.6, R2.1, R3.1, R4.1
unnamed: R20.1, R21.E
unnamed: D1.A, R1.2
unnamed: D2.C, IC1.2, L1.2
unnamed: C17.1, R18.1, R23.2
unnamed: C18.1, R19.1, R25.2
unnamed: P1.5.P, R12.2
unnamed: P1.0.P, R13.2
unnamed: M1:R6.1, P0.0.P
unnamed: IC4.3, R31.2
unnamed: LED1.A, R32.1
unnamed: LED2.A, R33.1
unnamed: M1:R1.1, P0.1.P
unnamed: M1:R7.1, P0.2.P
unnamed: M1:R8.1, P0.3.P
unnamed: M2:R6.1, P3.4.P
unnamed: M2:R1.1, P3.5.P
unnamed: M2:R7.1, P3.6.P
unnamed: P3.P, U1.17
unnamed: M2:R8.1, P3.7.P
unnamed: P57.P, R32.2
unnamed: P58.P, R33.2
unnamed: P1.P, U1.21
unnamed: P9.P, U1.20
unnamed: P2.P, U1.19
unnamed: P10.P, U1.18
unnamed: P11.P, U1.16
unnamed: P4.P, U1.15
unnamed: P12.P, U1.14
unnamed: P5.P, U1.13
unnamed: P13.P, U1.12
unnamed: P6.P, U1.11
unnamed: P14.P, U1.10
unnamed: P7.P, U1.9
unnamed: P15.P, U1.8
unnamed: P8.P, U1.7
unnamed: P16.P, U1.6
unnamed: P26.P, U1.23
unnamed: P36.P, U1.24
unnamed: P25.P, U1.25
unnamed: P35.P, U1.26
unnamed: P24.P, U1.27
unnamed: P34.P, U1.28
unnamed: P23.P, U1.29
unnamed: P33.P, U1.30
unnamed: P22.P, U1.31
unnamed: P32.P, U1.32
unnamed: P21.P, U1.33
unnamed: P31.P, U1.34
unnamed: P60.P, X4.2
unnamed: P17.P, U1.41
unnamed: P27.P, U1.42
SPEED: C16.1, P2.1.P, R21.S
VB: C11.+, C12.+, M1:Q1H.4, M1:Q2H.4, M2:Q1H.4, M2:Q2H.4, R1.1, R10.2, TP25.TP, TP26.TP, TP27.TP, TP28.TP, TP29.TP, TP30.TP, X1.1
VBUS: C13.1, P2.0.P, R10.1, R11.2
VDD: C1.1, C4.1, C9.1, C10.+, C21.1, IC2.3, IC3.8, IC4.5, R20.2, SWD1.5, TP1.PP, U1.1, U1.44
WA: M1:C1.2, M1:IC1.6, M1:Q1H.3, M1:Q1L.4, X2.1
WB: M2:C1.2, M2:IC1.6, M2:Q1H.3, M2:Q1L.4, X3.1

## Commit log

2018-09-19 pradine inicializacija
